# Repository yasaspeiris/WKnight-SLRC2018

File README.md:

# WKnight-SLRC2018

WKnight was made to compete in the Sri Lankan Robotics Challenge organized by the University of Moratuwa. 
The structure of this repo is as follows.

### Parts
Contains the STL files for the 3D printable parts. This includes the base, coin picking mechanism and gearing system.

### SLRC2019
This folder contains the code (for an Atmega2560). Each core component is split into a seperate .ino file. 

*colorsetup - Helper function for the colour sensor

*lightsandsw - Lights and switches

*main

*motorsetup - Contains motor control functions, white line/ wall / encoder PID Functions

*nrfsetup - NRF24L functions for wireless communication with a stationary robot

*path - path minimization

*QTRC - calibration and helper functions for the Pololu QTRC panel

*servosetup - servo control

*SLRC2019_19_Edited - global variables and definitions

*sonarsetup - ultrasonic sensor setup and control

*vlxsetup - TOF sensor (not used)

*wallfollow - wall following (not used)

### WKnightMEGA Breakout Board 
A breakout board for the Atmega2560 development board.

Full Instructions will be updated soon.

## Contributors
Pasindu Liyanage

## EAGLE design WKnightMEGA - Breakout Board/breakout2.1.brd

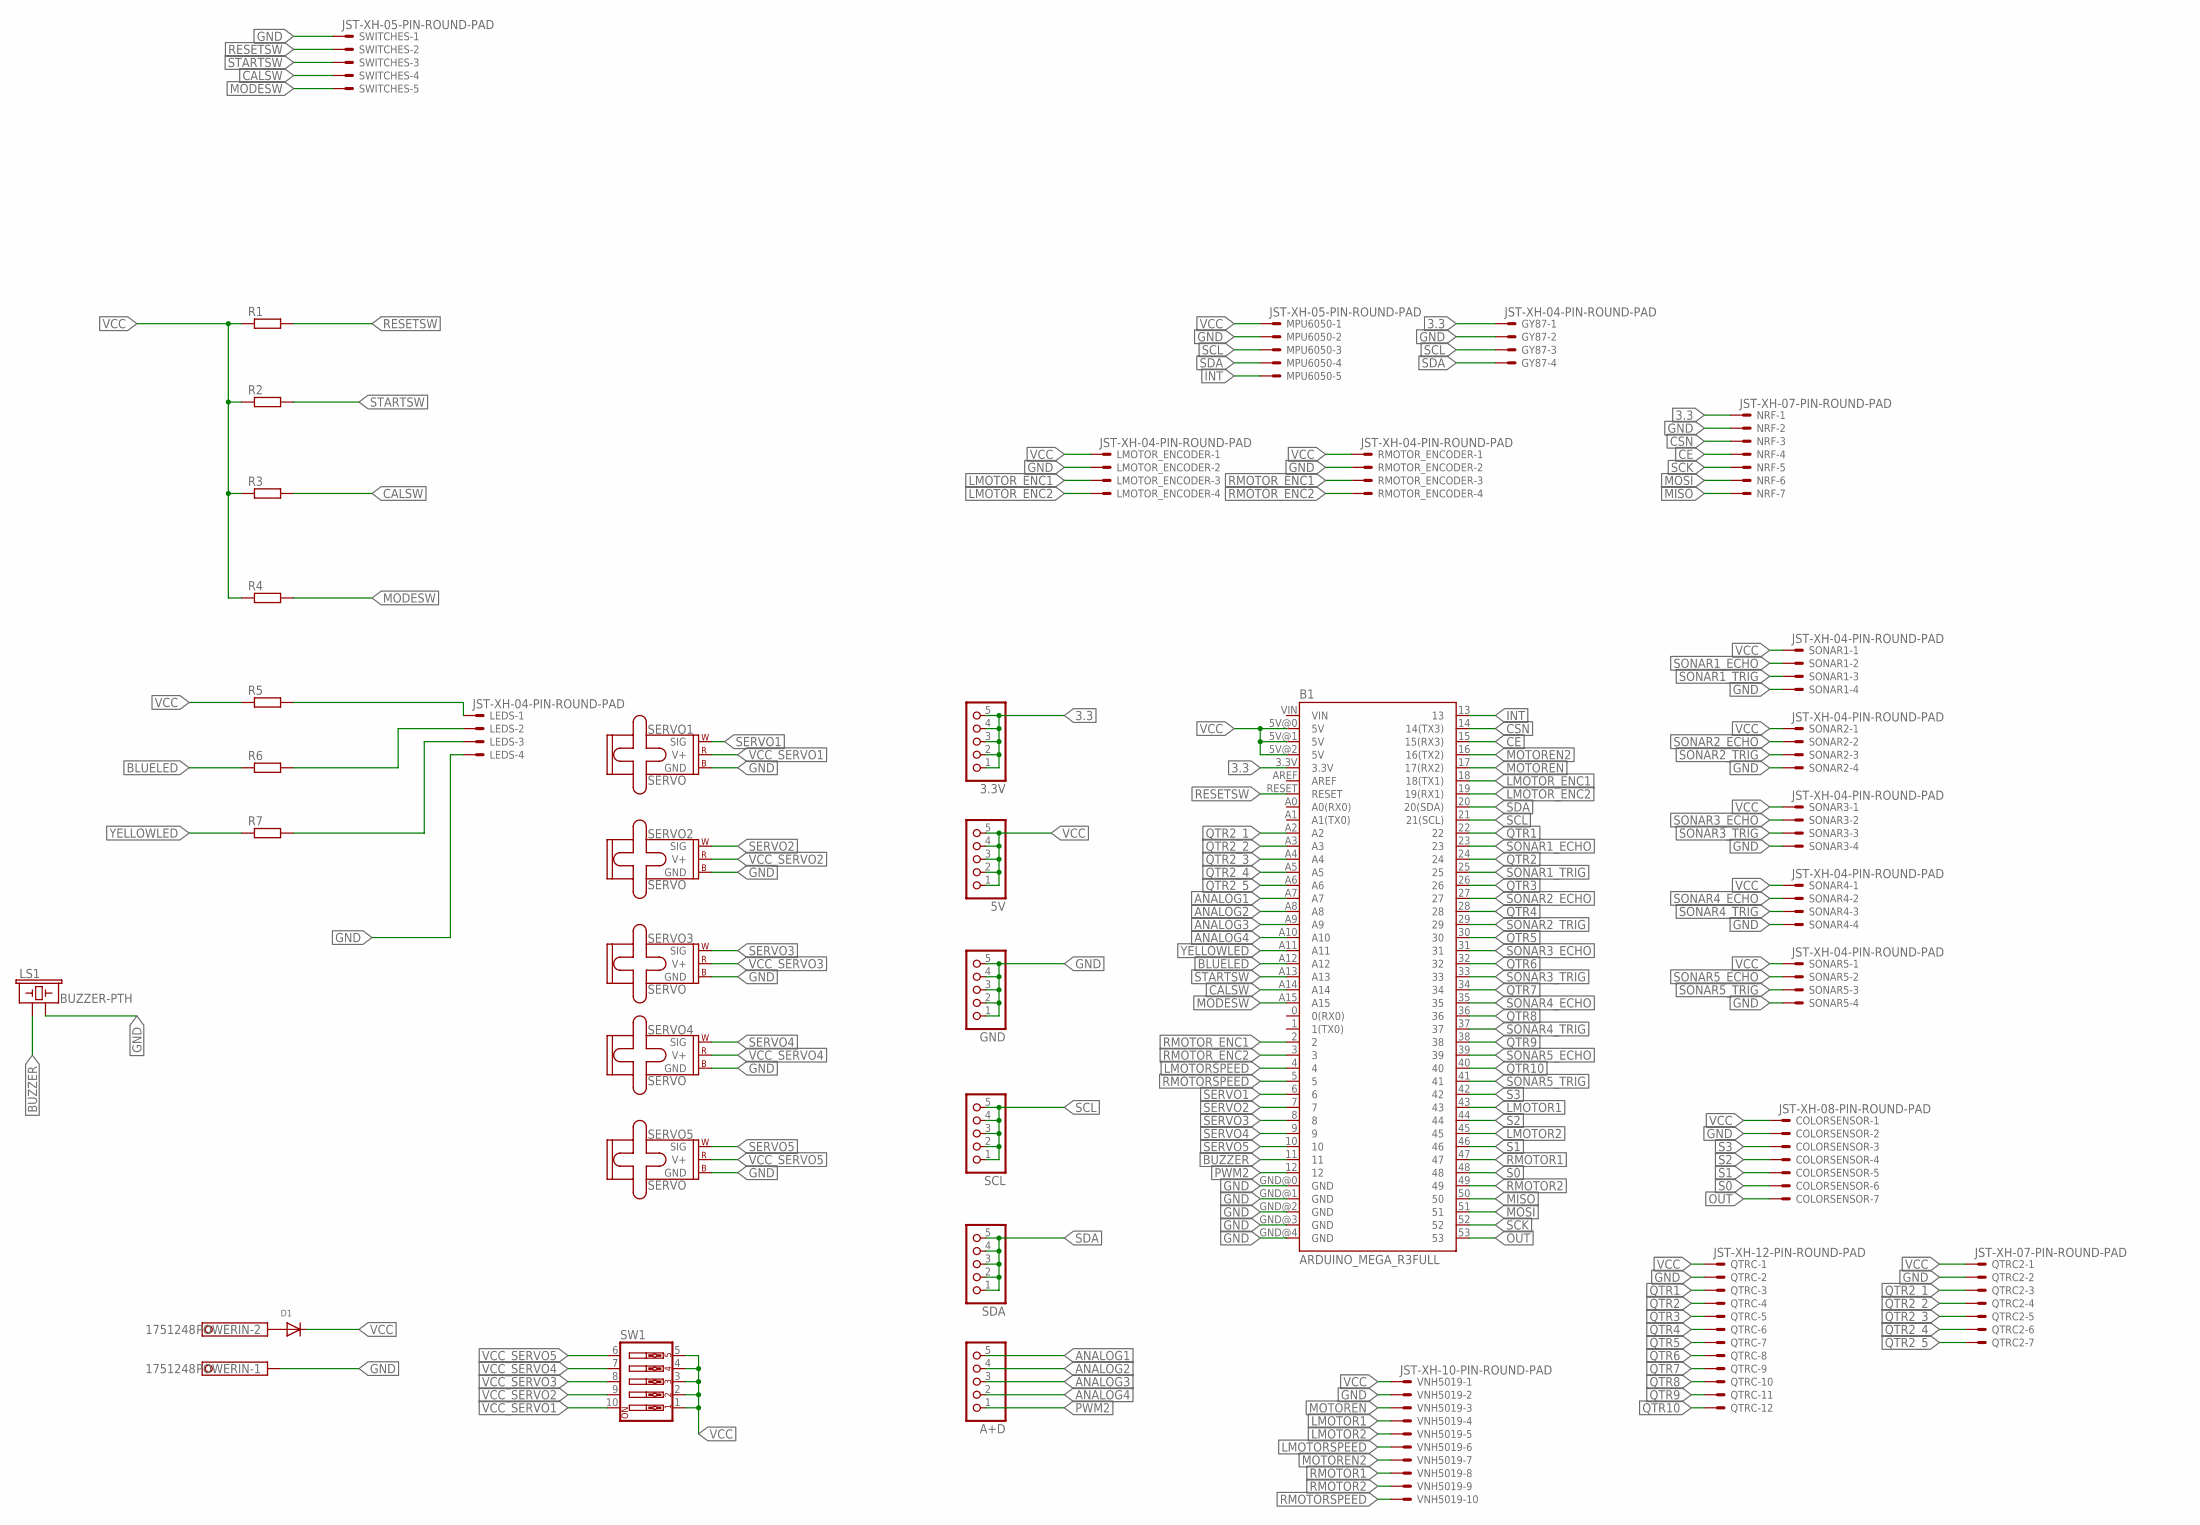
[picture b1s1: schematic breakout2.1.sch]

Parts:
3.3V, 5V: PINHD-1X55X2MM; 1_05X2MM
A+D: PINHD-1X55X2MM; 1_05X2MM
B1: ARDUINO_MEGA_R3FULL; ARDUINO_MEGA
COLORSENSOR: JST-XH-08-PIN-ROUND-PAD; JST-XH-08-PACKAGE-ROUND-PAD
D1: DIODEDO-1N4148; DO-1N4148
GND: PINHD-1X55X2MM; 1_05X2MM
GY87: JST-XH-04-PIN-ROUND-PAD; JST-XH-04-PACKAGE-ROUND-PAD
LEDS: JST-XH-04-PIN-ROUND-PAD; JST-XH-04-PACKAGE-ROUND-PAD
LMOTOR_ENCODER: JST-XH-04-PIN-ROUND-PAD; JST-XH-04-PACKAGE-ROUND-PAD
LS1: BUZZER-PTH; BUZZER-12MM
MPU6050: JST-XH-05-PIN-ROUND-PAD; JST-XH-05-PACKAGE-ROUND-PAD
NRF: JST-XH-07-PIN-ROUND-PAD; JST-XH-07-PACKAGE-ROUND-PAD
POWERIN: 1751248
QTRC: JST-XH-12-PIN-ROUND-PAD; JST-XH-12-PACKAGE-ROUND-PAD
QTRC2: JST-XH-07-PIN-ROUND-PAD; JST-XH-07-PACKAGE-ROUND-PAD
R1, R2, R3, R4, R5, R6, R7: R-EU_0204/7; 0204/7
RMOTOR_ENCODER: JST-XH-04-PIN-ROUND-PAD; JST-XH-04-PACKAGE-ROUND-PAD
SCL: PINHD-1X55X2MM; 1_05X2MM
SDA: PINHD-1X55X2MM; 1_05X2MM
SERVO1, SERVO2, SERVO3, SERVO4, SERVO5: SERVO; 1X03
SONAR1, SONAR2, SONAR3, SONAR4, SONAR5: JST-XH-04-PIN-ROUND-PAD; JST-XH-04-PACKAGE-ROUND-PAD
SW1: SW_DIP-5; EDG-05
SWITCHES: JST-XH-05-PIN-ROUND-PAD; JST-XH-05-PACKAGE-ROUND-PAD
VNH5019: JST-XH-10-PIN-ROUND-PAD; JST-XH-10-PACKAGE-ROUND-PAD

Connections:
3.3: 3.3V.1, 3.3V.2, 3.3V.3, 3.3V.4, 3.3V.5, B1.3.3V, GY87.1, NRF.1
ANALOG1: A+D.5, B1.A7
ANALOG2: A+D.4, B1.A8
ANALOG3: A+D.3, B1.A9
ANALOG4: A+D.2, B1.A10
BLUELED: B1.A12, R6.1
BUZZER: B1.11, LS1.+ (1)
CALSW: B1.A14, R3.2, SWITCHES.4
CE: B1.15 (15(RX3)), NRF.4
CSN: B1.14 (14(TX3)), NRF.3
GND: B1.GND@0 (GND), B1.GND@1 (GND), B1.GND@2 (GND), B1.GND@3 (GND), B1.GND@4 (GND), COLORSENSOR.2, GND.1, GND.2, GND.3, GND.4, GND.5, GY87.2, LEDS.4, LMOTOR_ENCODER.2, LS1.- (2), MPU6050.2, NRF.2, POWERIN.1, QTRC.2, QTRC2.2, RMOTOR_ENCODER.2, SERVO1.3 (GND), SERVO2.3 (GND), SERVO3.3 (GND), SERVO4.3 (GND), SERVO5.3 (GND), SONAR1.4, SONAR2.4, SONAR3.4, SONAR4.4, SONAR5.4, SWITCHES.1, VNH5019.2
INT: B1.13, MPU6050.5
LMOTOR1: B1.43, VNH5019.4
LMOTOR2: B1.45, VNH5019.5
LMOTORSPEED: B1.4, VNH5019.6
LMOTOR_ENC1: B1.18 (18(TX1)), LMOTOR_ENCODER.3
LMOTOR_ENC2: B1.19 (19(RX1)), LMOTOR_ENCODER.4
MISO: B1.50, NRF.7
MODESW: B1.A15, R4.2, SWITCHES.5
MOSI: B1.51, NRF.6
MOTOREN: B1.17 (17(RX2)), VNH5019.3
MOTOREN2: B1.16 (16(TX2)), VNH5019.7
unnamed: D1.A, POWERIN.2
unnamed: LEDS.2, R6.2
unnamed: LEDS.3, R7.2
unnamed: LEDS.1, R5.2
OUT: B1.53, COLORSENSOR.7
PWM2: A+D.1, B1.12
QTR1: B1.22, QTRC.3
QTR2: B1.24, QTRC.4
QTR2_1: B1.A2, QTRC2.3
QTR2_2: B1.A3, QTRC2.4
QTR2_3: B1.A4, QTRC2.5
QTR2_4: B1.A5, QTRC2.6
QTR2_5: B1.A6, QTRC2.7
QTR3: B1.26, QTRC.5
QTR4: B1.28, QTRC.6
QTR5: B1.30, QTRC.7
QTR6: B1.32, QTRC.8
QTR7: B1.34, QTRC.9
QTR8: B1.36, QTRC.10
QTR9: B1.38, QTRC.11
QTR10: B1.40, QTRC.12
RESETSW: B1.RESET, R1.2, SWITCHES.2
RMOTOR1: B1.47, VNH5019.8
RMOTOR2: B1.49, VNH5019.9
RMOTORSPEED: B1.5, VNH5019.10
RMOTOR_ENC1: B1.2, RMOTOR_ENCODER.3
RMOTOR_ENC2: B1.3, RMOTOR_ENCODER.4
S0: B1.48, COLORSENSOR.6
S1: B1.46, COLORSENSOR.5
S2: B1.44, COLORSENSOR.4
S3: B1.42, COLORSENSOR.3
SCK: B1.52, NRF.5
SCL: B1.21 (21(SCL)), GY87.3, MPU6050.3, SCL.1, SCL.2, SCL.3, SCL.4, SCL.5
SDA: B1.20 (20(SDA)), GY87.4, MPU6050.4, SDA.1, SDA.2, SDA.3, SDA.4, SDA.5
SERVO1: B1.6, SERVO1.1 (SIG)
SERVO2: B1.7, SERVO2.1 (SIG)
SERVO3: B1.8, SERVO3.1 (SIG)
SERVO4: B1.9, SERVO4.1 (SIG)
SERVO5: B1.10, SERVO5.1 (SIG)
SONAR1_ECHO: B1.23, SONAR1.2
SONAR1_TRIG: B1.25, SONAR1.3
SONAR2_ECHO: B1.27, SONAR2.2
SONAR2_TRIG: B1.29, SONAR2.3
SONAR3_ECHO: B1.31, SONAR3.2
SONAR3_TRIG: B1.33, SONAR3.3
SONAR4_ECHO: B1.35, SONAR4.2
SONAR4_TRIG: B1.37, SONAR4.3
SONAR5_ECHO: B1.39, SONAR5.2
SONAR5_TRIG: B1.41, SONAR5.3
STARTSW: B1.A13, R2.2, SWITCHES.3
VCC: 5V.1, 5V.2, 5V.3, 5V.4, 5V.5, B1.5V@0 (5V), B1.5V@1 (5V), B1.5V@2 (5V), COLORSENSOR.1, D1.C, LMOTOR_ENCODER.1, MPU6050.1, QTRC.1, QTRC2.1, R1.1, R2.1, R3.1, R4.1, R5.1, RMOTOR_ENCODER.1, SONAR1.1, SONAR2.1, SONAR3.1, SONAR4.1, SONAR5.1, SW1.1, SW1.2, SW1.3, SW1.4, SW1.5, VNH5019.1
VCC_SERVO1: SERVO1.2 (V+), SW1.10
VCC_SERVO2: SERVO2.2 (V+), SW1.9
VCC_SERVO3: SERVO3.2 (V+), SW1.8
VCC_SERVO4: SERVO4.2 (V+), SW1.7
VCC_SERVO5: SERVO5.2 (V+), SW1.6
YELLOWLED: B1.A11, R7.1

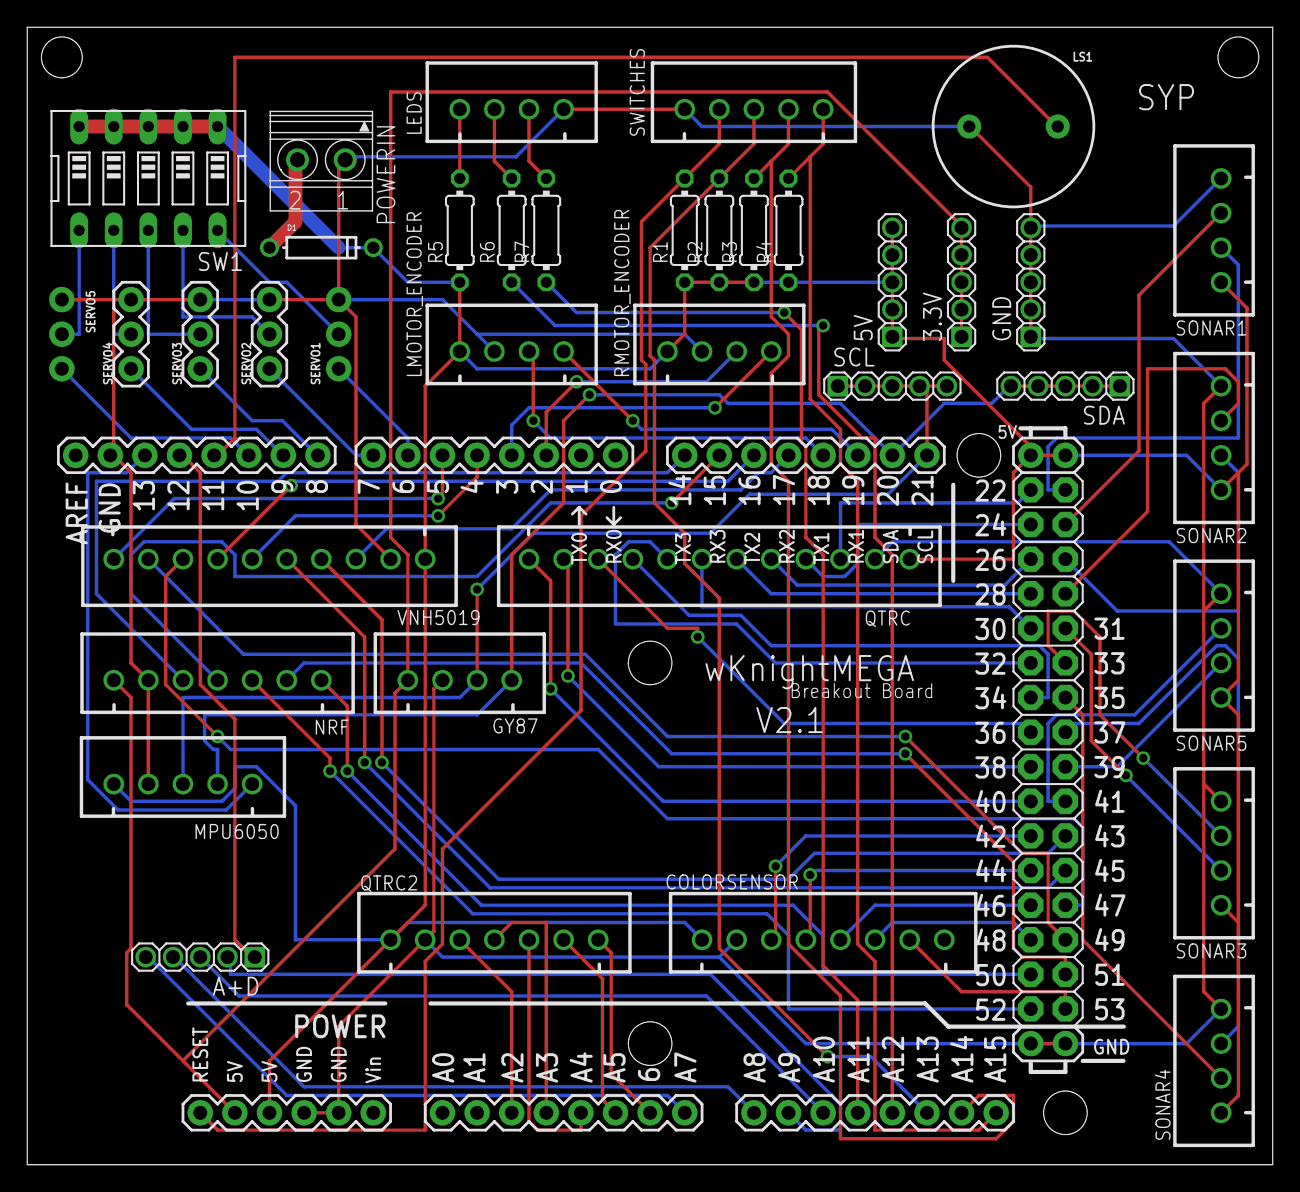
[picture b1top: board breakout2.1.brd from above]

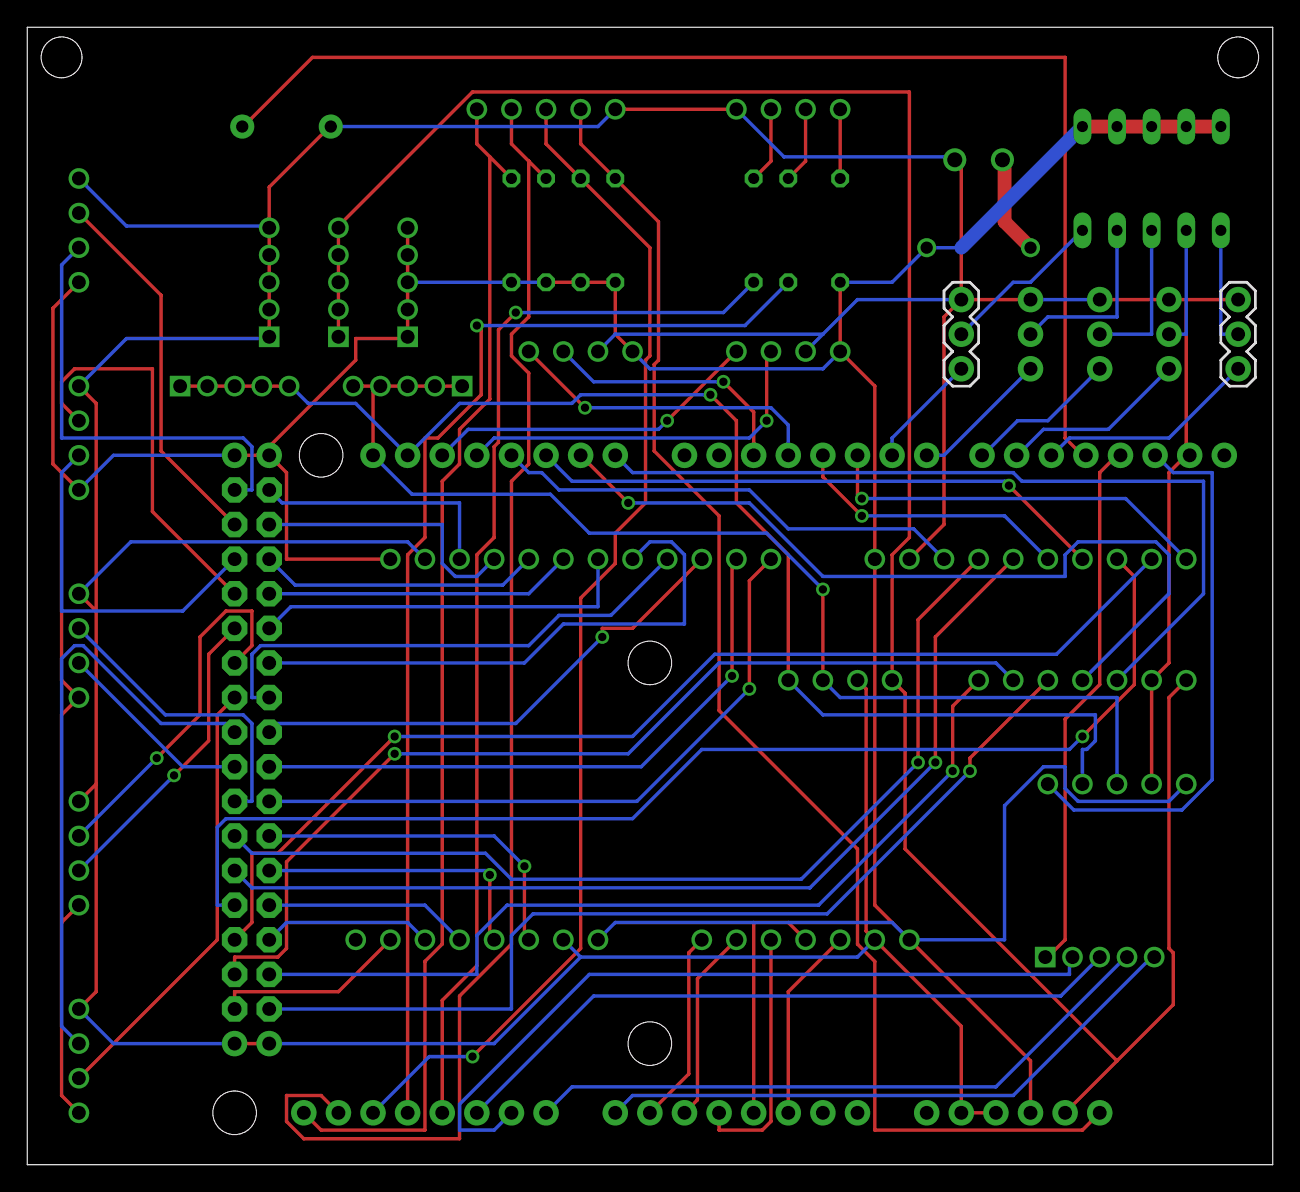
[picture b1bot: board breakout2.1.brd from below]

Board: 2 copper layers, 91.4 x 83.5 mm, 39 parts (2 on the bottom side), 79 nets.

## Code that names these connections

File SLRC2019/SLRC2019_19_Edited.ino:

  int SPEED  = 60;
int pwmconstrain = 255;
#define REVERSESPEED 60
#define TURNSPEED 140

int OVERSHOOT_TICKS = 520;
#define REVERSETICKS 100
#define FRONTTICKS 800

#define PADDING 200
#define MAPPED_PADDING 170
#define RETURN_PADDING 200

#define BOXOVERSHOOT 100

#define COINS 4
int which_turn = 0;

int totalSum = 0;


#define Kp 0.03
#define Kd 1.2 
#define Ki 0

/*===================================================================

          //QTRC Variables

  =====================================================================*/
#include <QTRSensors.h>
#define NUM_SENSORS   10     // number of sensors used
#define TIMEOUT       2500  // waits for 2500 microseconds for sensor outputs to go low
#define EMITTER_PIN   QTR_NO_EMITTER_PIN

// sensors 0 through 10 are connected to digital pins 3 through 10, respectively
QTRSensorsRC qtrrc((unsigned char[]) {
  38, 40, 22, 24, 26, 28, 30, 32, 34, 36  //38, 40, 22, 24, 26, 28, 30, 32, 34, 36
},
NUM_SENSORS, TIMEOUT, EMITTER_PIN);
unsigned int sensorValues[NUM_SENSORS];
unsigned int sensorRead[NUM_SENSORS];
unsigned int SensorPanelVal = 0;
unsigned int position = 0;
int _lastValue = 0;



/*===================================================================

          //Sonar Variables

  =====================================================================*/
#include <NewPing.h>

#define MAX_DISTANCE_FRONT 20 // Maximum distance we want to ping for (in centimeters). Maximum sensor distance is rated at 400-500cm.

#define SONAR1_ECHO 23
#define SONAR1_TRIG 25

#define SONAR2_ECHO 27
#define SONAR2_TRIG 29

#define SONAR3_ECHO 31
#define SONAR3_TRIG 33

#define SONAR4_ECHO 35
#define SONAR4_TRIG 37

#define SONAR5_ECHO 39
#define SONAR5_TRIG 41

NewPing sonar1(SONAR1_TRIG, SONAR1_ECHO, MAX_DISTANCE_FRONT); 
NewPing sonar2(SONAR2_TRIG, SONAR2_ECHO, MAX_DISTANCE_FRONT);
NewPing sonar3(SONAR3_TRIG, SONAR3_ECHO, MAX_DISTANCE_FRONT);
NewPing sonar4(SONAR4_TRIG, SONAR4_ECHO, MAX_DISTANCE_FRONT);
NewPing sonar5(SONAR5_TRIG, SONAR5_ECHO, MAX_DISTANCE_FRONT);
int i;
int tmp = 0;
int front, right, left,slantleft,slantright = 0;

/*===================================================================

          //Front VLX

  =====================================================================*/

#include <Wire.h>
#include <VL53L0X.h>

VL53L0X sensor;

/*===================================================================

          //Motor Driver Variables

  =====================================================================*/

#define LMOTORSPEED 4 //L PWM Pin
#define RMOTORSPEED 5 // R PWM Pin

#define LMOTOR1 43
#define LMOTOR2 45

#define RMOTOR1 49
#define RMOTOR2 47

#define MOTOREN 17
#define MOTOREN2 16

#define LMOTOR_ENC1 19
#define LMOTOR_ENC2 18

#define RMOTOR_ENC1 3
#define RMOTOR_ENC2 2

/* =============================================

    Encoder Variables

    ============================================
*/
#define ENCODER_OPTIMIZE_INTERRUPTS
#include <Encoder.h>

Encoder MasterENC(LMOTOR_ENC2, LMOTOR_ENC1);
Encoder SlaveENC(RMOTOR_ENC1, RMOTOR_ENC2);
long totalTicks = 0;

#define ticksperrevolutioncheapmotor 768
#define ticksperrevolution 816
#define ticksperinchcheapo 87 //cheap motor encoder pulses per inch (ZGA-31)
#define ticksperinch 94.45 //pololu motor encoder pulses per inch
#define tickspermm 7.42

int i_motord = 0;
boolean startingfromstop = 1;

int MasterPower = 0;
int SlavePower = 0;
int MaxPower = 0;

int error = 0;
int lasterror = 0;
int sumerr = 0;



/*===================================================================

          //Servo Variables

  =====================================================================*/

#include <Servo.h>

#define SERVO1 6
#define SERVO2 7
#define SERVO3 8
#define SERVO4 9
#define SERVO5 10

Servo grabber, lifter1, lifter2;


int servotmp = 0;

/*===================================================================

          //Pretty Lights and Switches

  ===================================================================== */

#define MODESW A13 //
bool startpressed = 0;
#define STARTSWITCH A15
bool modepressed = 0;
#define CALSW A14
bool calpressed = 0;

#define BLUELED A12
#define YELLOWLED A11
#define GREENLED A7


/*===================================================================

          //Path Variables

  ===================================================================== */

boolean nodeflag = 0;
int gotboxes = 0;
char doaction = 'S'; //start
char temp = 't';
char nextmove;
char path[100] = "";
char path_togoback[100] = "";
int path_length = 0;
int path_length_togoback = 0;

/*===================================================================

          //NRF Variables

  ===================================================================== */


#include <SPI.h>
#include "RF24.h"

RF24 myRadio (15, 14);
byte addresses[][6] = {"0"};

struct package
{
  int sum = 0;
  char command = 'n';

};


typedef struct package Package;
Package data;

String inString = "";
int rcvval = 0;
int prvrcv = 0;
char cmd = 'n';


/*===================================================================

          //Color Sensor

  ===================================================================== */

#define S0 48
#define S1 46
#define S2 44
#define S3 42
#define sensorOut 12
int frequency = 0;


/*===================================================================

          //Wall Follow

  ===================================================================== */

int lastfound;



/*===================================================================

          //PCA9685

  ===================================================================== */
#include <Adafruit_PWMServoDriver.h>
Adafruit_PWMServoDriver pwm = Adafruit_PWMServoDriver();
#define SERVOMIN  150 // this is the 'minimum' pulse length count (out of 4096)
#define SERVOMAX  600 // this is the 'maximum' pulse length count (out of 4096)

#define COINTOSSERLEFT 0
#define COINTOSSERRIGHT 1
#define MAINARMLEFT 2
#define MAINARMRIGHT 3

#define EJECTRIGHT 5
#define EJECTLEFT 4

#define LEFTPANE 7
#define RIGHTPANE 6

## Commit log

2019-01-22 initial source commit
2019-01-22 second commit
2019-01-25 parts commit
2019-01-25 Breakout Board

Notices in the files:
parts and their libraries:
SparkFun-Boards: Licensing: Creative Commons ShareAlike 4.0 International - https://creativecommons.org/licenses/by-sa/4.0
